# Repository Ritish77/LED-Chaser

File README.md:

# 🔥 LED Chaser Circuit using 555 Timer & CD4017 (PCB Design)

## 📌 Overview
This project demonstrates an LED chaser circuit where LEDs glow sequentially to create a running light effect. The design uses a 555 timer in astable mode to generate clock pulses and a CD4017 decade counter to drive multiple LEDs.

---

## ⚙️ Components Used
- NE555 Timer IC  
- CD4017 Decade Counter IC  
- Resistors (150Ω, 10kΩ)  
- Capacitors (10µF, 10nF)  
- LEDs (10–11 LEDs)  
- 9V Power Supply  
- PCB designed using Autodesk Eagle  

---

## 🧠 Working Principle
- The **555 timer** operates in astable mode and generates clock pulses  
- These pulses are fed into the **CD4017 counter IC**  
- CD4017 activates outputs sequentially (Q0 → Q9)  
- Each output drives an LED, producing a chasing light effect  

---

## 🖥️ Design Details
- Schematic designed using Autodesk Eagle  
- PCB layout manually routed  
- Through-hole components used  
- Design Rule Check (DRC) performed  
- Proper component placement and routing ensured  

---

## 🖼️ Project Images

### 🔹 Schematic

### 🔹 PCB Layout

---

## 📂 Files Included
- `schematic.sch` → Eagle schematic file  
- `pcb.brd` → PCB layout file  
- `/images` → Circuit and PCB images  
- `README.md`  

---

## 🚀 How to Use
1. Open schematic and board files in Autodesk Eagle  
2. Verify connections and components  
3. Generate PCB layout  
4. Fabricate or simulate the circuit  
5. Provide 9V supply  
6. Observe LED chasing sequence  

---

## 🎯 Learning Outcomes
- Understanding of 555 timer (astable mode)  
- Working of CD4017 decade counter  
- Hands-on PCB design using Eagle  
- Routing and layout optimization  
- Practical hardware design workflow  

---

## 📊 Key Highlights
- Designed complete hardware system from schematic to PCB  
- Implemented real-world circuit without microcontroller  
- Gained hands-on PCB design experience  

---

## 👤 Author
**Ritish**  
Electronics & Communication Engineering Student

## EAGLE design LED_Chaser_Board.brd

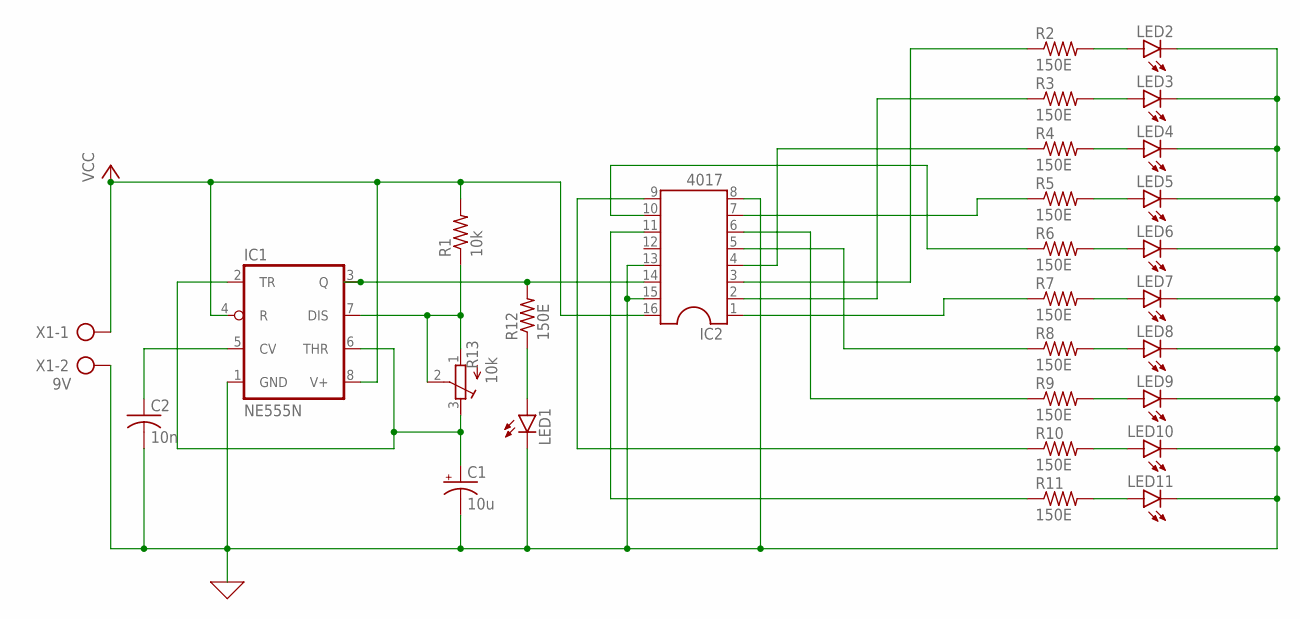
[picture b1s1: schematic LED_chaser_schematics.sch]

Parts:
C1: 10u; E2,5-6
C2: 10n; C025-024X044
IC1: NE555N; DIL08
IC2: 4017; DIL16
LED1, LED2, LED3, LED4, LED5, LED6, LED7, LED8, LED9, LED10, LED11: LED5MM
R1: 10k; 0207/10
R2, R3, R4, R5, R6, R7, R8, R9, R10, R11, R12: 150E; 0207/10
R13: 10k; RTRIM3299W
X1: 9V; AK500/2

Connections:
0: C1.-, C2.2, IC1.1 (GND), IC2.8, IC2.13, IC2.15, LED1.K (C), LED2.K (C), LED3.K (C), LED4.K (C), LED5.K (C), LED6.K (C), LED7.K (C), LED8.K (C), LED9.K (C), LED10.K (C), LED11.K (C), X1.2
unnamed: LED2.A, R2.2
unnamed: LED3.A, R3.2
unnamed: LED4.A, R4.2
unnamed: LED5.A, R5.2
unnamed: LED6.A, R6.2
unnamed: LED7.A, R7.2
unnamed: LED8.A, R8.2
unnamed: LED9.A, R9.2
unnamed: LED10.A, R10.2
unnamed: LED11.A, R11.2
unnamed: IC2.4, R4.1
unnamed: IC2.2, R3.1
unnamed: IC2.6, R9.1
unnamed: IC2.7, R5.1
unnamed: IC2.10, R6.1
unnamed: IC2.9, R10.1
unnamed: IC2.5, R8.1
unnamed: IC2.1, R7.1
unnamed: IC2.11, R11.1
unnamed: IC2.3, R2.1
unnamed: IC1.3 (Q), IC2.14, R12.2
unnamed: LED1.A, R12.1
unnamed: IC1.7 (DIS), R1.1, R13.1 (A), R13.2 (S)
unnamed: C1.+, IC1.2 (TR), IC1.6 (THR), R13.3 (E)
unnamed: C2.1, IC1.5 (CV)
VCC: IC1.4 (R), IC1.8 (V+), IC2.16, R1.2, X1.1

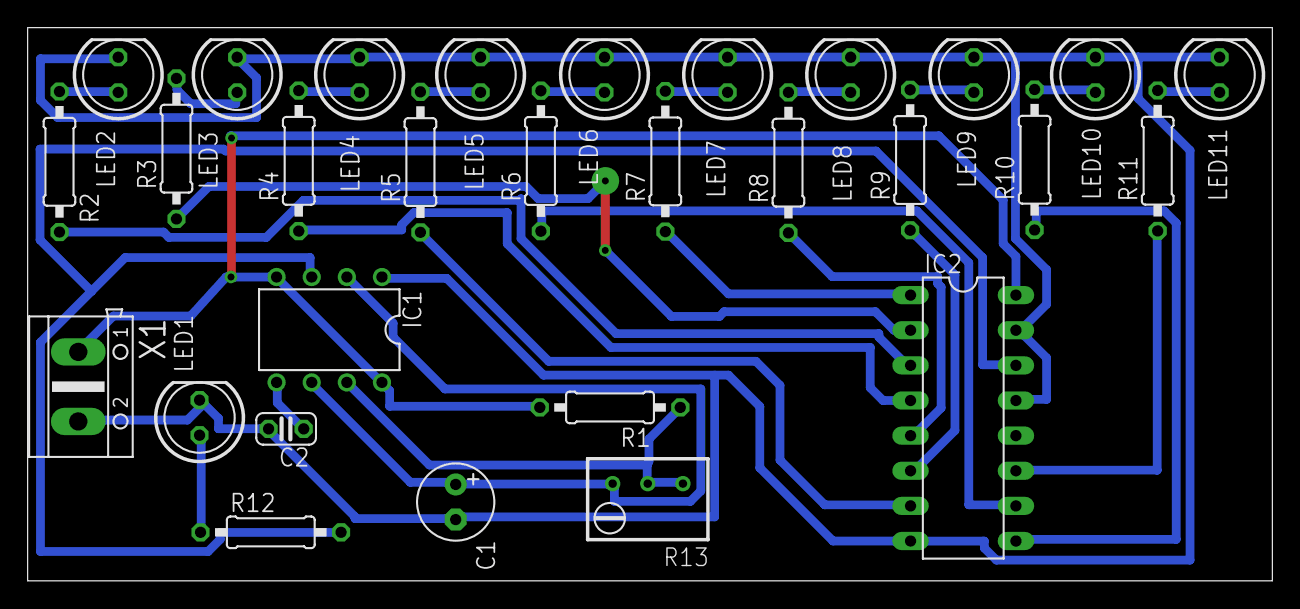
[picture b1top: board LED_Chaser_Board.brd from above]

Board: 2 copper layers, 90.0 x 40.0 mm, 29 parts (0 on the bottom side), 27 nets.

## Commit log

2026-03-29 README for LED Chaser Circuit project
    README to provide detailed project overview, components, working principle, design details, images, usage instructions, learning outcomes, and author information.
